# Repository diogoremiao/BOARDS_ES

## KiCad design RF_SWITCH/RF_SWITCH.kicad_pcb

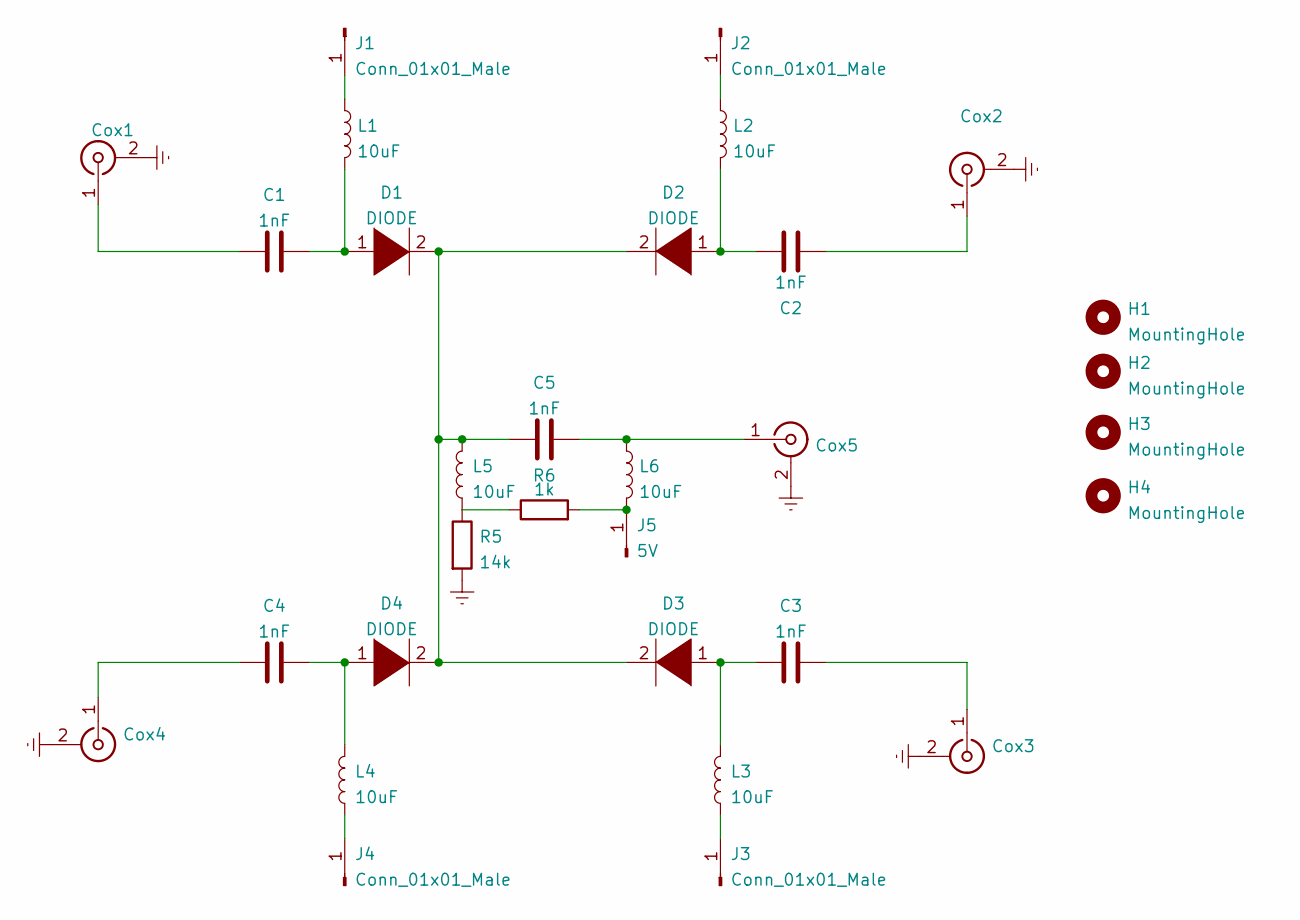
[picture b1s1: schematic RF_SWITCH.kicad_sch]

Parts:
C1, C2, C3, C4, C5: 1nF; C_0805_2012Metric
Cox1, Cox2, Cox3, Cox4, Cox5: Conn_Coaxial; SMA_Molex_73251-1153_EdgeMount_Horizontal
D1, D2, D3, D4: DIODE; D_0402_1005Metric
H1, H2, H3, H4: MountingHole; MountingHole_2.1mm
J1, J2, J3, J4: Conn_01x01_Male; Pin_D1.0mm_L10.0mm
J5: 5V; Pin_D1.0mm_L10.0mm
L1, L2, L3, L4, L5, L6: 10uF; L_0805_2012Metric
R5: 14k; R_0805_2012Metric
R6: 1k; R_0805_2012Metric

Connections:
Earth: Cox1.2 (Ext), Cox2.2 (Ext), Cox3.2 (Ext), Cox4.2 (Ext), Cox5.2 (Ext), R5.2
unnamed: C1.2, D1.1 (K), L1.2
unnamed: C2.1, Cox2.1 (In)
unnamed: C2.2, D2.1 (K), L2.2
unnamed: C3.1, Cox3.1 (In)
unnamed: C3.2, D3.1 (K), L3.2
unnamed: C4.2, D4.1 (K), L4.2
unnamed: C5.1, D1.2 (A), D2.2 (A), D3.2 (A), D4.2 (A), L5.2
unnamed: C5.2, Cox5.1 (In), L6.1
unnamed: C1.1, Cox1.1 (In)
unnamed: C4.1, Cox4.1 (In)
unnamed: J1.1, L1.1
unnamed: J2.1, L2.1
unnamed: J3.1, L3.1
unnamed: J4.1, L4.1
unnamed: J5.1, L6.2, R6.2
unnamed: L5.1, R5.1, R6.1

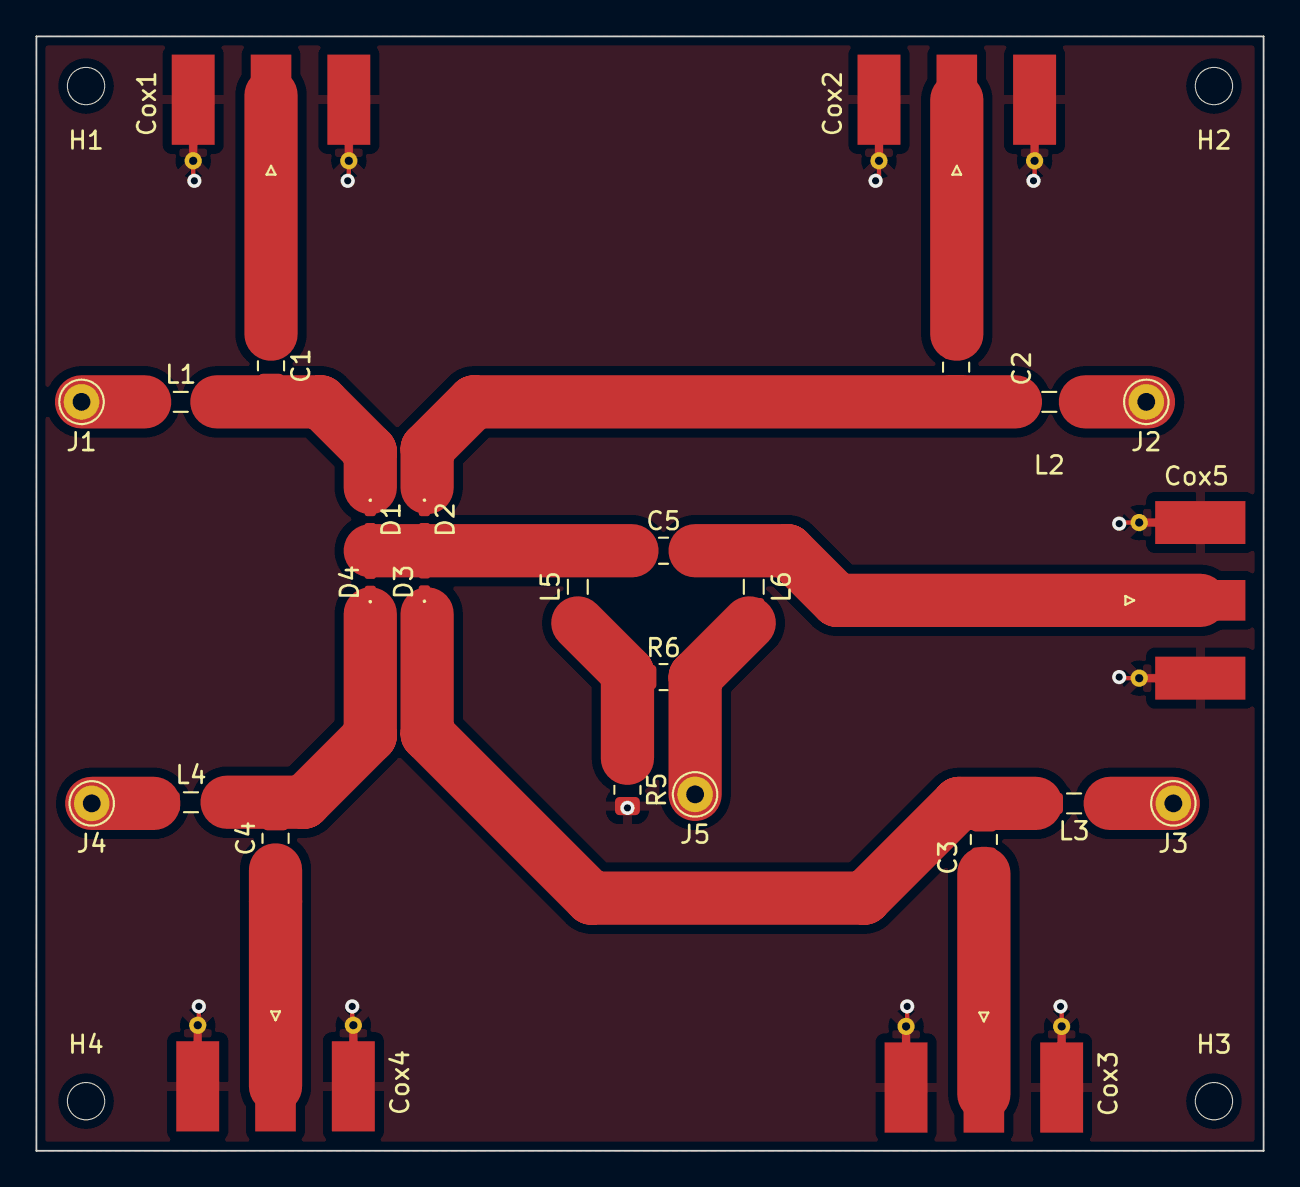
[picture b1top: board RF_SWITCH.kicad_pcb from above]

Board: 2 copper layers, 69.1 x 62.7 mm, 31 parts (0 on the bottom side), 17 nets.

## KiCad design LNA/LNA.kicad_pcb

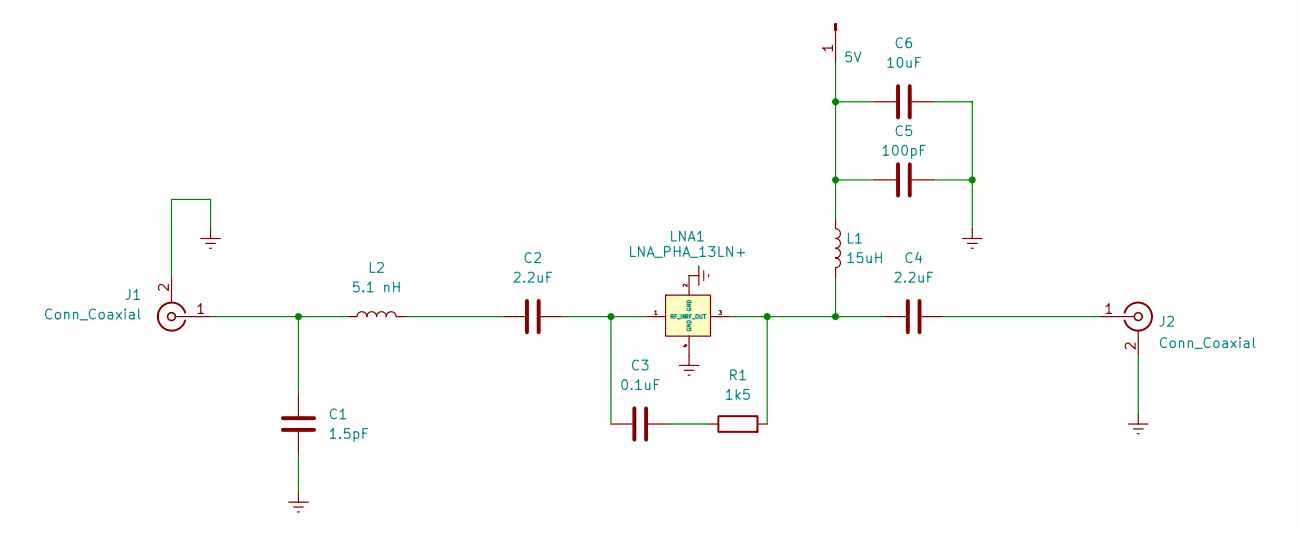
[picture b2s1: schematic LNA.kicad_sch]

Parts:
C1: 1.5pF; C_0805_2012Metric
C2, C4: 2.2uF; C_0805_2012Metric
C3: 0.1uF; C_0805_2012Metric
C5: 100pF; C_0805_2012Metric
C6: 10uF; C_0805_2012Metric
Con1: 5V; Pin_D1.0mm_L10.0mm
J1, J2: Conn_Coaxial; SMA_Molex_73251-1153_EdgeMount_Horizontal
L1: 15uH; L_1008_2520Metric
L2: 5.1 nH; L_0603_1608Metric
LNA1: LNA_PHA_13LN+; LNA_PHA-13LN+
R1: 1k5; R_0805_2012Metric

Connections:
Earth: C1.2, C5.2, C6.2, J1.2 (Ext), J2.2 (Ext), LNA1.2 (GND), LNA1.4 (GND)
unnamed: C1.1, J1.1 (In), L2.1
unnamed: C2.1, L2.2
unnamed: C2.2, C3.1, LNA1.1 (RF_IN)
unnamed: C3.2, R1.1
unnamed: C4.1, L1.2, LNA1.3 (RF_OUT), R1.2
unnamed: C4.2, J2.1 (In)
unnamed: C5.1, C6.1, Con1.1, L1.1

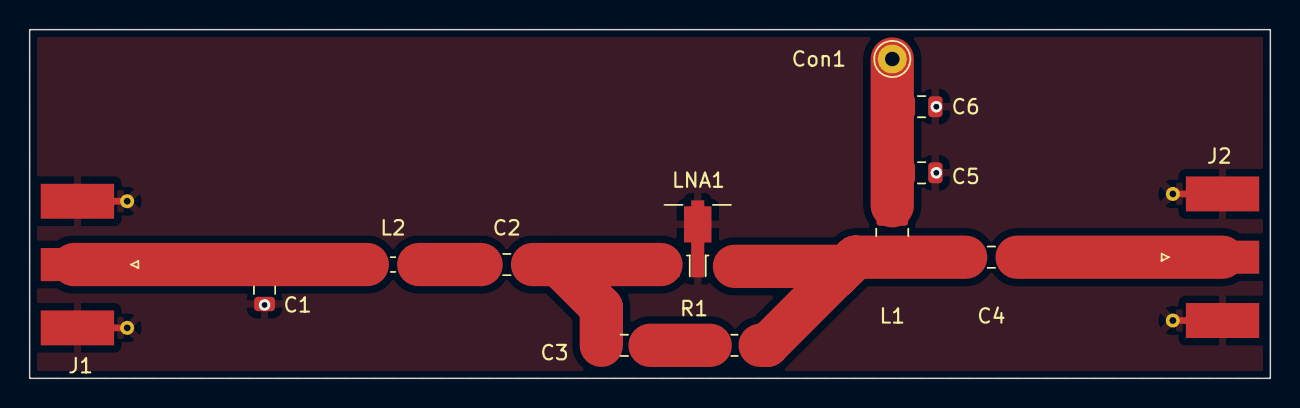
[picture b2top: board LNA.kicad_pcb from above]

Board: 2 copper layers, 85.9 x 24.1 mm, 13 parts (0 on the bottom side), 8 nets.

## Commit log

2021-12-05 Remi Stuff
2022-01-10 final
